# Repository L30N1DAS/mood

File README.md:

## Table of contents

* [Rationale](README.md#rationale)
* [Safety](README.md#safety)
* [Bill of materials (BOM)](README.md#bill-of-materials)
* [The Circuit](README.md#the-circuit)
* [KiCAD](README.md#kicad)
* [Design](README.md#design)
* [Arduino Software](README.md#arduino-software)

---

## Rationale

**Welcome to you're doom!**

Ahem, I mean welcome to the PCB design portion of your summer camp!

This project was selected to introduce a variety of topics including:

* Circuit schematics / basic electronics
* PCB design (Computer-Aided Design using KiCAD)
* Hardware / Software trojans
* Hardware / Software bugs

By the end of these two weeks you will have a basic understanding of how to 
layout and build a basic circuit and what vulnerabilities it may have 
(unintentional or otherwise).

---

## Safety

A (brief) word on safety.  All of the equipment and materials used in this project
are safe, so long as they are used properly.

Our goal is to make sure that over the two weeks of this project you are instructed 
on how to perform each of the steps needed to manufacture a PCB safely.  **Please do
NOT turn on any of the machines or use any of the equipment until you have had the 
safety overview for that equipment or process.** 

Similarly, if you are unsure on the safe way to perform some process just ask one of 
our several lab assistants.  We are happy to help!  There will be additional safety
instructions covered over the course of the two weeks and all relevant safety documents
will be kept in the `Safety` folder in this repository.

---

## Bill of materials

Most of the materials have already been inlcuded in your Elegoo kit.  These include:

* Arduino project board
* Various items from the Elegoo kit:
  * 2x Tri-color LED
  * 3x 330Ω Resistors
  * Buzzer
  * L293D
  * DC Motor
  * IR Receiver and Remote Control
  * 2μF Capacitor

Other items needed include:

* Copper clad PCB board
* Solder
* PCB Fabrication Equipment

---

## The Circuit

The circuit started as this:

This is the schematic:

This is the PCB layout:

This is the final product:

---

## KiCAD

We will be using the open source Computer-Aided Drawing / Electronics Design Automation (CAD/EDA) suite [KiCad](https://www.kicad.org/).  This software can be installed freely on Windows/Mac/Linuxand is very powerful.  Further documentation and cheatsheets can be found in the `KiCad` folder of this repository.

---

## Design

The project aims to design a remote-controlled color-changing light system with RGB LEDs controlled by three PWM signals. The system will be operated using an IR remote controller, allowing users to adjust LED colors and brightness levels to create various vibrant RGB combinations. Notably, as a part of the project's educational goals, an intentional inclusion of "malicious" code will be introduced. This demonstration will emphasize the importance of secure coding practices, as the code will play the E1M1 DOOM song when a specific button sequence is entered. The project's primary focus is on exploring LED control technology, color customization, and the implications of unsecured coding practices. Safety measures will not be implemented, as the project's central objective is to highlight the potential risks associated with inadequate security measures. The project seeks to provide users with an informative and insightful experience while demonstrating the significance of security in electronic systems.

---

## Ardunio Software 

[The code can be found here.](https://github.com/wrightedu/mood/tree/main/updated_mood/updated_mood_code)

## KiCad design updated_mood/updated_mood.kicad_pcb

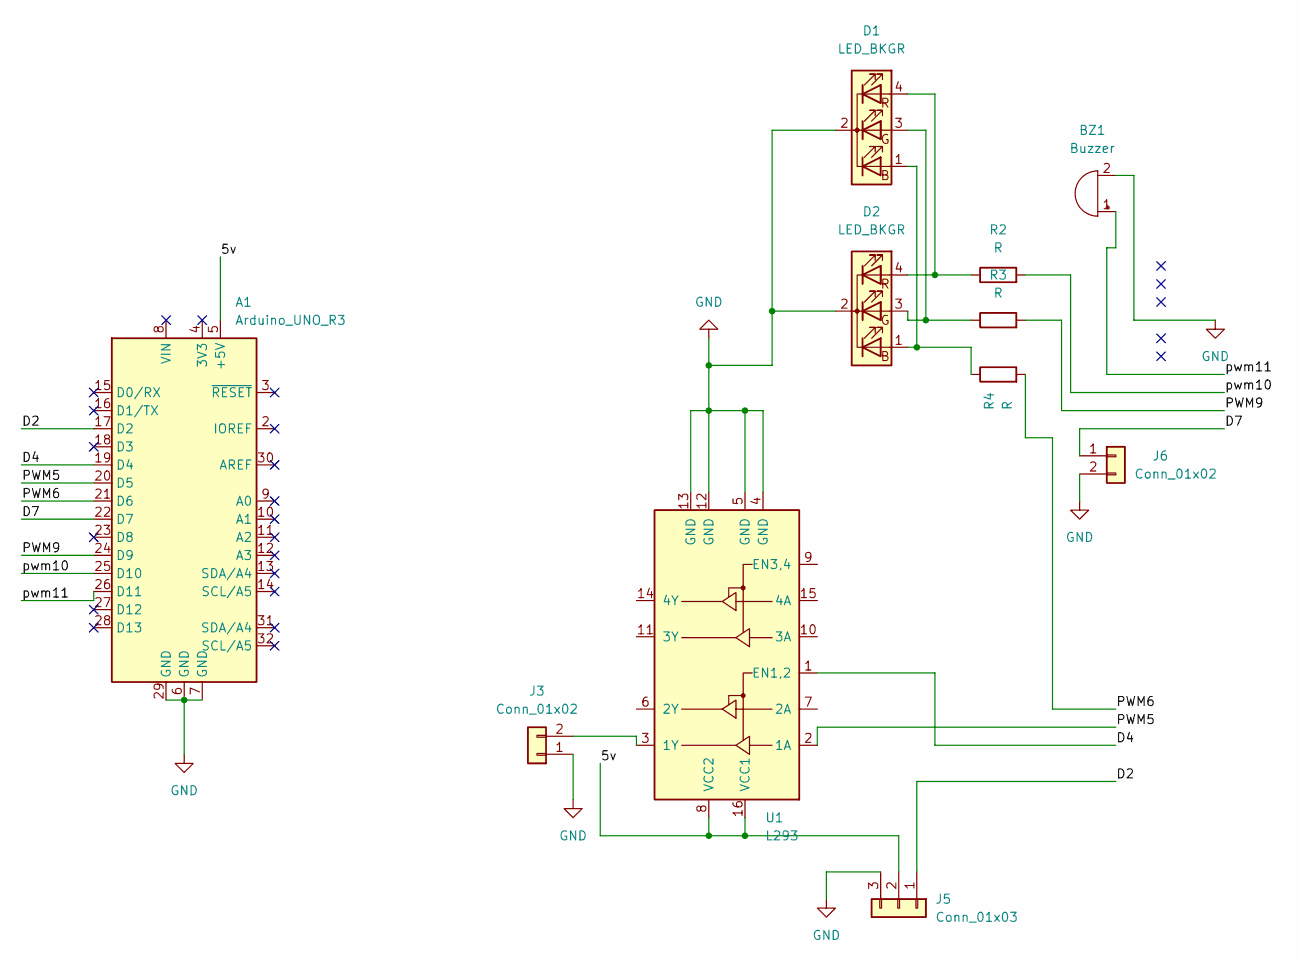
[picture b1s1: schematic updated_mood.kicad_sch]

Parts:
A1: Arduino_UNO_R3
BZ1: Buzzer; Buzzer_12x9.5RM7.6
D1, D2: LED_BKGR; LED_D5.0mm-4_RGB_Wide_Pins
J3, J6: Conn_01x02; PinHeader_1x02_P2.54mm_Vertical
J5: Conn_01x03; PinHeader_1x03_P2.54mm_Vertical
R2, R3, R4: R; R_Axial_DIN0207_L6.3mm_D2.5mm_P7.62mm_Horizontal
U1: L293; DIP-16_W7.62mm

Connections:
/5v: A1.5 (+5V), J5.2, U1.8 (VCC2), U1.16 (VCC1)
/D2: A1.17 (D2), J5.1
/D4: A1.19 (D4), U1.1 (EN1,2)
/D7: A1.22 (D7), J6.1
/PWM5: A1.20 (D5), U1.2 (1A)
/PWM6: A1.21 (D6), R4.2
/PWM9: A1.24 (D9), R3.2
/pwm10: A1.25 (D10), R2.2
/pwm11: A1.26 (D11), BZ1.1 (-)
GND: A1.6 (GND), A1.7 (GND), A1.29 (GND), BZ1.2 (+), D1.2 (K), D2.2 (K), J3.1, J5.3, J6.2, U1.4 (GND), U1.5 (GND), U1.12 (GND), U1.13 (GND)
unnamed: D1.1 (BA), D2.1 (BA), R4.1
unnamed: D1.3 (GA), D2.3 (GA), R3.1
unnamed: D1.4 (RA), D2.4 (RA), R2.1
unnamed: J3.2, U1.3 (1Y)

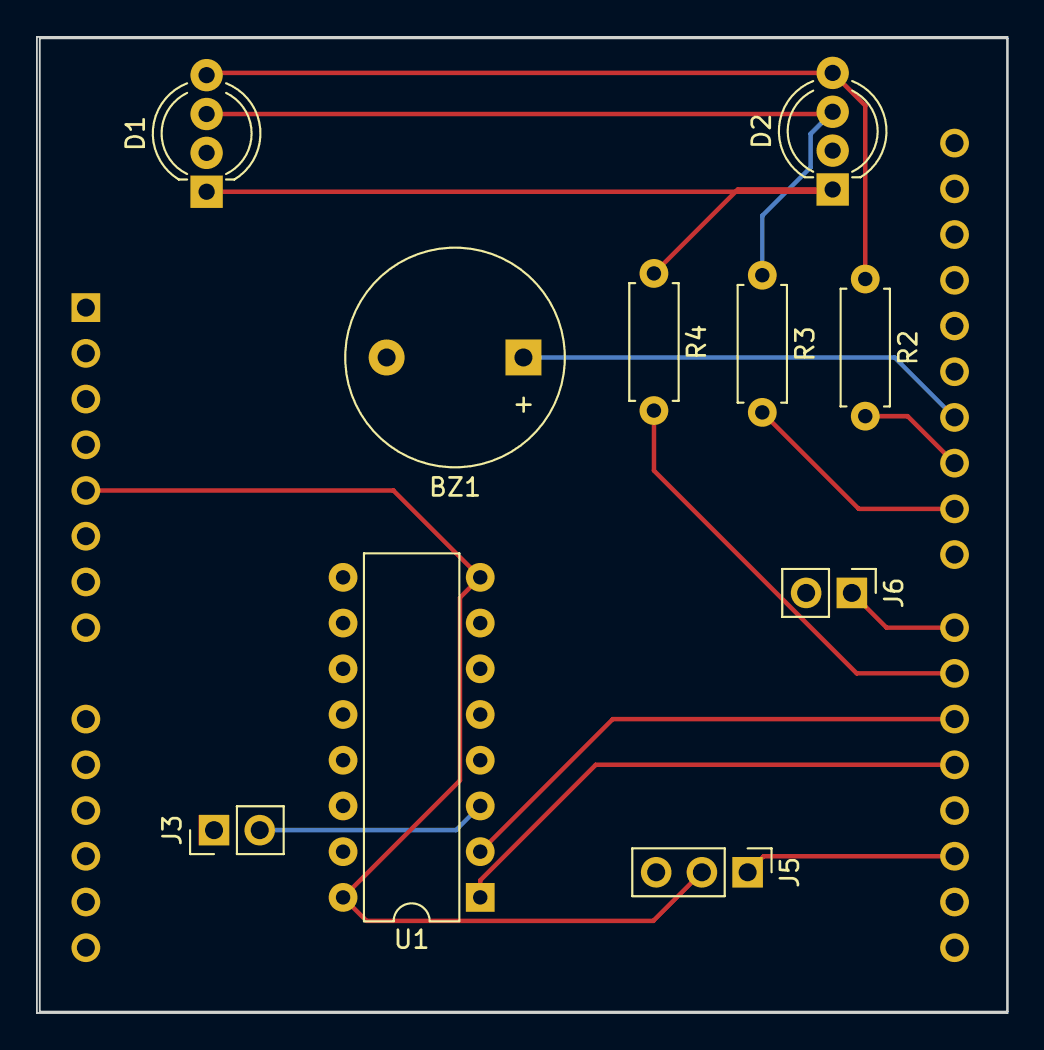
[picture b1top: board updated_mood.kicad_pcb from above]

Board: 2 copper layers, 53.9 x 54.2 mm, 11 parts (1 on the bottom side), 14 nets.

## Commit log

2023-07-05 init
2023-07-05 circuit cheatsheet
2023-07-05 push it again
2023-07-07 add seven seg file
2023-07-10 init mood schematic
2023-07-14 Uploading BILLY BOARD
2023-07-18 Uploaded mood images
2023-07-19 Removed THIS_THING_HERE, Uploaded updated_mood
2023-07-19 Added mood breadboard image
2023-07-19 Changed names and edited schematic
2023-07-19 Uploaded code
2023-07-19 Update README.md
    Added some images
2023-07-19 Fixed formatting
2023-07-19 Linked code in readme
2023-07-19 Added more components used
2023-07-19 Added design portion
2023-07-19 Fixed various typos, punctuation, and added images.
2024-06-29 cleaning up
    * removed second RGB led
    * cleaned up circuit diagram
    * added notes to KiCAD README
